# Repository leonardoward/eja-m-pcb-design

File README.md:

# EJA M v1.0

The new EJA M v1.0 is an upgrade/replacement of my older PCB designs: [Buoy A v1.0](https://github.com/leonardoward/eja-intelligent-buoy-a-electronics), [Buoy B v1.0](https://github.com/leonardoward/eja-intelligent-buoy-b-electronics), and [Onboard Gateway v1.0](https://github.com/leonardoward/eja-onboard-gateway-electronics). The design includes the following features:

- USB C Port with Electromagnetic Compatibility (EMC)
- FTDI (FT260S-U) with an Auto Reset Circuit for the ESP32
- ESP32
- GPS Module
- LoRa Transceiver
- Real-time Clock (RTC)
- Connector for a Servo Motor
- 5V 2A Stepup (for the Servo Motor)
- 3.3V Battery Charging Circuit
- Connector for a 3 axis accelerometer
- Circuit to measure the battery level
- 3.3V 3A SEPIC Converter
- On-OFF circuit for a Button
- Access to unused pins in the ESP32

This repository contains the Kicad project (including Gerber files) and a more detailed description about the implementation of the different features in the design.

## Table of Contents

1. [Hardware Design](#getting-started)
    1. [USB C Port with Electromagnetic Compatibility EMC](#usb-c-port-with-electromagnetic-compatibility-emc)
    2. [FTDI FT260S](#ftdi-ft260s)
    3. [Auto Reset Circuit for the ESP32](#auto-reset-circuit-for-the-esp32)
    4. [ESP32](#esp32)
    5. [GPS](#gps)
    6. [LoRa](#lora)
    7. [Real time Clock RTC](#real-time-clock-rtc)
    8. [Servo Motor Connector](#servo-motor-connector)
    9. [5V 2A Stepup](#5v-2a-stepup)
    10. [Accelerometer Connector](#accelerometer-connector)
    11. [Battery Charging Circuit](#battery-charging-circuit)
    12. [Battery Level](#battery-level)
    13. [3V3 3A SEPIC Converter](#3v3-3a-sepic-converter)
    14. [ON-OFF Led](#on-off-led)
    15. [ON-OFF Button Circuit](#on-off-button-circuit)
    16. [Extra Header](#extra-header)
2. [PCB Dimensions and Boundaries](#pcb-dimensions-and-boundaries)
3. [3D Model](#3d-model)
4. [Bill of Materials](#bill-of-materials)
    1. [PCB Components](#pcb-components)
    2. [Externals Components](#externals-components)

## Hardware Design

### USB C Port with Electromagnetic Compatibility EMC

Everything starts with the USB C port, we have chosen this type of USB because it's size and because of the growing trend of using this port to charge and communicate with portable devices.

We have included [Transient Voltage Suppression (TVS) diodes](https://www.digikey.com/en/products/detail/comchip-technology/CPDT6-5V4-HF/1121118) and [Ferrite Beads](https://www.digikey.com/en/products/detail/fair-rite-products-corp/2508056017Y0/8594301) to reduce the Electromagnetic Interference (EMI). These [protections for the USB port](https://www.rs-online.com/designspark/usb-port-protection) will add compliance with the [EMC regulations and standards](https://learnemc.com/emc-regulations-and-standards) from the  Federal Communications Commission (FCC) and the European Union.   

**[Back to top](#table-of-contents)**

### FTDI FT260S

The design includes the [FT260S-U](https://www.digikey.com/en/products/detail/ftdi-future-technology-devices-international-ltd/FT260S-U/6124909), a USB TO UART/I2C FTDI that will be used to program the ESP32.

**[Back to top](#table-of-contents)**

### Auto Reset Circuit for the ESP32

The design includes an auto reset circuit that uses RTS and DTR to reset and put in bootloader mode the [ESP32](https://www.digikey.com/en/products/detail/espressif-systems/ESP32-WROOM-32D-4MB/9381716). For more information about this circuit, these blogs [(1)](https://forum.micropython.org/viewtopic.php?f=18&t=4966) [(2)](https://forums.adafruit.com/viewtopic.php?f=57&p=483993#p487891) can be useful.

**[Back to top](#table-of-contents)**

### ESP32

The main microcontroller in the PCB is the [ESP32](https://www.digikey.com/en/products/detail/espressif-systems/ESP32-WROOM-32D-4MB/9381716), the following image shows the signals dedicated to the different pins. The ESP32 is connected to the [FTDI](https://www.digikey.com/en/products/detail/ftdi-future-technology-devices-international-ltd/FT260S-U/6124909), a [GPS](https://lcsc.com/product-detail/Satellite-Positioning-Modules_ZHONGKEWEI-ATGM332D-5N31_C128659.html), a [LoRa transceiver](https://www.digikey.com/en/products/detail/rf-solutions/RFM95W-915S2/6564923), a connector for a servo motor, a [real-time clock](https://www.digikey.com/en/products/detail/maxim-integrated/DS3231M-TRL/2402421?s=N4IgTCBcDaICIGUDMYkEYCyBqAKgJQBkBhHAWgDk4QBdAXyA), a circuit to measure the battery level, a connector for an [accelerometer](https://www.digikey.com/en/products/detail/adafruit-industries-llc/4097/9951931?s=N4IgTCBcDaIIwFYwA4C0KDsAWVA5AIiALoC%2BQA), and a few headers to provide access for the unused peripherals.

**[Back to top](#table-of-contents)**

### GPS

The selected GPS is the [ATGM332D-5N31](https://lcsc.com/product-detail/Satellite-Positioning-Modules_ZHONGKEWEI-ATGM332D-5N31_C128659.html), one the modules tested previously in our [Development Board for GPS Modules](https://hackaday.io/project/173457-2021-hdp-dream-team-eja/log/196269-gps-antenova-m20050-1-and-atgm332d-5n31-dev-board). The schematic is very simple, it has a decoupling capacitors (C2), a [U.FL connector](https://www.digikey.com/en/products/detail/hirose-electric-co-ltd/U-FL-R-SMT-1-10/2391570) for an external antenna (J4) and a [Coin Cell Battery Holder](https://www.digikey.com/en/products/detail/linx-technologies-inc/BAT-HLD-001-THM/3044009) (J2).

**[Back to top](#table-of-contents)**

### LoRa

The selected LoRa transceiver is the [RFM95W-915S2](https://www.digikey.com/en/products/detail/rf-solutions/RFM95W-915S2/6564923), the same module tested in our [Development Board for LoRa](https://hackaday.io/project/173457-2021-hdp-dream-team-eja/log/196116-lora-rfm95w-915s2-development-board). The schematic contains a [U.FL connector](https://www.digikey.com/en/products/detail/hirose-electric-co-ltd/U-FL-R-SMT-1-10/2391570) for an external antenna (J9).

**[Back to top](#table-of-contents)**

### Real time Clock RTC

The design includes a dedicated RTC, the [DS3231M](https://www.digikey.com/en/products/detail/maxim-integrated/DS3231M-TRL/2402421?s=N4IgTCBcDaICIGUDMYkEYCyBqAKgJQBkBhHAWgDk4QBdAXyA).

**[Back to top](#table-of-contents)**

### Servo Motor Connector

There is a 1x3 header connector for a Servo Motor, the 5V for the servo is provided by a 5V 2A Stepup.

**[Back to top](#table-of-contents)**

### 5V 2A Stepup

The design includes the [TPS61030PWR](http://digikey.com/en/products/detail/texas-instruments/TPS61030PWPR/550685?s=N4IgTCBcDa4JwDYC0BGALGlyVIHIBEQBdAXyA), a boost converter with a 4A switch current, to provide the 5V for the Servo motor. The schematic contains the components for a 5V 2A output, following the design procedure that starts on the page 13 in the datasheet.

**[Back to top](#table-of-contents)**

### Accelerometer Connector

There is a connector for the [ADXL343 3 axis accelerometer](https://www.digikey.com/en/products/detail/adafruit-industries-llc/4097/9951931?s=N4IgTCBcDaIIwFYwA4C0KDsAWVA5AIiALoC%2BQA), a 1x9 header was used even though it only manages the signals VDD, GND, SCL and SDA, in case we want to use more connections for the accelerometer in future versions.

**[Back to top](#table-of-contents)**

### Battery Charging Circuit

To charge the 3.3V battery the design includes the [TP4056](https://www.lcsc.com/product-detail/Battery-Management-ICs_TPOWER-TP4056_C382139.html), a 1A Standalone Linear Li-lon Battery Charger. The schematic includes a green led to show the user that the battery is charged and a red led to show the user that the battery is charging. There is a [Battery Holder for a 18650 battery](https://www.digikey.com/en/products/detail/mpd-memory-protection-devices/BH-18650-PC/3029216?s=N4IgTCBcDaIEIAkC0BGAHANgKwAYkAUBhJAOQBEQBdAXyA) (J5) and an additional 1x2 header (J7) in case we want to use a different 3.3V battery.  There is also a 1x2 header (J3) to use a different type of connection for the charger (instead of the USB C), for example we can connect and test a QI Wireless Charger.

**[Back to top](#table-of-contents)**

### Battery Level

The design contains a circuit to measure a battery level, it is a simple resistor divider calculated for a range of 2.7V to 4.2V, the normal range for the 18650 Li-Ion Battery that will be used in the design.

Those values for the resistor divider give the following range for the ADC:

- Maximum voltage: 4.2V * (2M / (0.806M + 2M)) = 2.99V
- Minimum voltage: 2.7V * (2M / (0.806M + 2M)) = 1.92V

That means that the ADC from the ESP32 will be reading analog values from 1.92V to 2.99V from the battery measurement circuit.

For more information about measuring lithium battery voltage visit the following [link](https://devzone.nordicsemi.com/nordic/nordic-blog/b/blog/posts/measuring-lithium-battery-voltage-with-nrf52).

**[Back to top](#table-of-contents)**

### 3V3 3A SEPIC Converter

Since the voltage of the battery can change from 2.7V (discharged) to 4.2V (charged), a SEPIC converter is included to provide a constant 3.3V to the digital circuits regardless of the changes in the input voltage from the battery. The selected SEPIC converter is the [LTC3113EFE#TRPBF](https://www.digikey.com/en/products/detail/analog-devices-inc/LTC3113EFE-TRPBF/2521714?s=N4IgTCBcDaIDIBUDCBmAjGlBRAYlgxAgEoAKAQjkggLQByAIiALoC%2BQA).

**Note**: The resistor R32 is a jumper that connects VDD to 3V3. R33 is a jumper that connects VDD to the battery. Do not solder both at the same time, it will create a short circuit between 3.3V from the SEPIC and the voltage from the battery. R32 and R33 are included just in case the SEPIC converter doesn't work and we have to connect the circuit directly to the battery.

**Summary: Do not solder R33**.

**[Back to top](#table-of-contents)**

### ON-OFF Led

There is  Green Led that turns on with the 3.3V from the SEPIC converter, it will notify the user/developer that the device is ON or OFF.

**[Back to top](#table-of-contents)**

### ON-OFF Button Circuit

The design contains a [LTC2954ITS8-1#TRPBF](https://www.digikey.com/en/products/detail/analog-devices-inc/LTC2954ITS8-1-TRPBF/1621452?s=N4IgTCBcDaIDIBUDCYCcBWALASQQZQA4BaARgGIEAlABQCEAxJBIgOQBEQBdAXyA), a pushbutton ON/OFF controller that manages the power supply (enables the 3.3V SEPIC) via a pushbutton interface.

**[Back to top](#table-of-contents)**

### Extra Header

The design includes an 1x06 header to provide access for some of the unused pins in the ESP32.

**[Back to top](#table-of-contents)**

## PCB Dimensions and Boundaries

The dimensions of the PCB are dictated by the maximum available space inside the buoy, from the enclosure design we where able to define the size of the PCB: 97.5 mm x 51.2 mm.

In the back layer there is a restricted region, that can't contain any components because the PCB is directly in contact with the enclosure in that region, those are the boundaries of the back layer. Through hole footprints where not be placed in that section, even if the footprint is placed in the front layer.

**[Back to top](#table-of-contents)**

## 3D Model

The following images show the front and back layers of the PCB.

**[Back to top](#table-of-contents)**

## Bill of Materials

### PCB Components

| Reference | Quantity |
| ------------- | ------------- |
| [PCB](https://www.pcbway.com/)  | 1 |
| [47 µF ±20% 6.3V Ceramic Capacitor 0805](https://www.digikey.com/en/products/detail/taiyo-yuden/JMK212BBJ476MG-T/4970731)  | 1 |
| [10 µF ±10% 6.3V Ceramic Capacitor 0805](https://www.digikey.com/en/products/detail/samsung-electro-mechanics/CL21A106KQCLNNC/3888062)  | 4 |
| [12 pF ±5% 50V Ceramic Capacitor 0805](https://www.digikey.com/en/products/detail/stackpole-electronics-inc/CML0805C0G120JT50V/10660016)  | 1 |
| [680 pF ±10% 25V Ceramic Capacitor 0805](https://www.digikey.com/en/products/detail/w%C3%BCrth-elektronik/885012207059/5455614)  | 1 |
| [47 pF ±5% 16V Ceramic Capacitor 0805](https://www.digikey.com/en/products/detail/w%C3%BCrth-elektronik/885012007014/5453673)  | 3 |
| [100 µF ±20% 6.3V Ceramic Capacitor 1210](https://www.digikey.com/en/products/detail/murata-electronics/GRM32EE70J107ME15L/5027618)  | 1 |
| [0.1 µF ±10% 50V Ceramic Capacitor 0805](https://www.digikey.com/en/products/detail/avx-corporation/08055C104KAT2A/563505)  | 3 |
| [4.7 µF ±10% 6.3V Ceramic Capacitor 0805](https://www.digikey.com/en/products/detail/samsung-electro-mechanics/CL21A475KQFNNNE/3886856)  | 1 |
| [1 µF ±10% 16V Ceramic Capacitor 0805](https://www.digikey.com/en/products/detail/yageo/CC0805KKX7R7BB105/2103103)  | 4 |
| [2.2 µF ±10% 10V Ceramic Capacitor 0805](https://www.digikey.com/en/products/detail/samsung-electro-mechanics/CL21B225KPFNNNE/3886846)  | 1 |
| [220 µF Tantalum Capacitors 10V 2917](https://www.digikey.com/en/products/detail/nemco/PCT220-10HK/13236441)  | 1 |
| [0.033 µF ±10% 50V Ceramic Capacitor 0805](https://www.digikey.com/en/products/detail/w%C3%BCrth-elektronik/885012207095/5453932)  | 1 |
| [Orange 601nm LED - Discrete 2.1V 0805](https://www.digikey.com/en/products/detail/sunled/XZMOK54W-1/4745796)  | 1 |
| [Green 520nm LED - Discrete 3.2V 0805](https://www.digikey.com/en/products/detail/w%C3%BCrth-elektronik/150080GS75000/4489915)  | 2 |
| [TVS Diode 15V Clamp 5A (8/20µs) SOT-23-6](https://www.digikey.com/en/products/detail/comchip-technology/CPDT6-5V4-HF/1121118)  | 1 |
| [Red 630nm LED - Discrete 1.9V 0805](https://www.digikey.com/en/products/detail/w%C3%BCrth-elektronik/150080SS75000/4489921)  | 1 |
| [Yellow 590nm LED - Discrete 2V 0805](https://www.digikey.com/en/products/detail/everlight-electronics-co-ltd/QTLP630C3TR/2675901)  | 1 |
| [1 Signal Line Ferrite Bead 0805 300mA 350mOhm](https://www.digikey.com/en/products/detail/fair-rite-products-corp/2508056017Y0/8594301)  | 2 |
| [USB-C USB 3.2 Gen 2 Receptacle Connector](https://www.digikey.com/en/products/detail/cui-devices/UJ31-CH-G2-SMT-TR/8024057)  | 1 |
| [Battery Retainer Coin, 20.0mm 1 Cell PC Pin](https://www.digikey.com/en/products/detail/linx-technologies-inc/BAT-HLD-001-THM/3044009)  | 1 |
| [U.FL (UMCC) Connector Receptacle](https://www.digikey.com/en/products/detail/hirose-electric-co-ltd/U-FL-R-SMT-1-10/2391570)  | 2 |
| [Battery Holder (Open) 18650 1 Cell PC Pin](https://www.digikey.com/en/products/detail/mpd-memory-protection-devices/BH-18650-PC/3029216)  | 1 |
| [2 Position Terminal Block Horizontal](https://www.digikey.com/en/products/detail/on-shore-technology-inc/OSTTC022162/614558)  | 1 |
| [2.2 µH Inductor 15 A 7mOhm Max](https://www.digikey.com/en/products/detail/sumida-america-components-inc/104CDMCCDS-2R2MC/5812436)  | 1 |
| [5.5 µH Inductor 10 A 10.3mOhm](https://www.digikey.com/en/products/detail/w%C3%BCrth-elektronik/744325550/1638576)  | 1 |
| [Bipolar (BJT) Transistor NPN 30V 600mA SOT-23-3](https://www.digikey.com/en/products/detail/onsemi/MMBT2222LT1G/919595)  | 3 |
| [1 MOhms ±1% 0.125W Chip Resistor 0805](https://www.digikey.com/en/products/detail/stackpole-electronics-inc/RMCF0805FT1M00/1760080)  | 2 |
| [90.9 kOhms ±1% 0.125W Chip Resistor 0805](https://www.digikey.com/en/products/detail/stackpole-electronics-inc/RMCF0805FT90K9/1760265)  | 1 |
| [620 Ohms ±5% 0.125W Chip Resistor 0805](https://www.digikey.com/en/products/detail/yageo/RC0805JR-07620RL/728357)  | 5 |
| [5.1 KOhms ±1% 0.125W Chip Resistor 0805](https://www.digikey.com/en/products/detail/stackpole-electronics-inc/RMCF0805FT5K10/1760394)  | 3 |
| [49.9 KOhms ±1% 0.125W Chip Resistor 0805](https://www.digikey.com/en/products/detail/stackpole-electronics-inc/RMCF0805FT49K9/1760272)  | 1 |
| [825 kOhms ±0.5% 0.125W Chip Resistor 0805](https://www.digikey.com/en/products/detail/panasonic-electronic-components/ERA-6AED8253V/3481309)  | 1 |
| [182 kOhms ±1% 0.25W Chip Resistor 0805](https://www.digikey.com/en/products/detail/koa-speer-electronics-inc/RK73H2ATTD1823F/10234151)  | 1 |
| [1.2 kOhms ±5% 0.125W Chip Resistor 0805](https://www.digikey.com/en/products/detail/yageo/RC0805JR-071K2L/728224)  | 1 |
| [6.49 kOhms ±1% 0.125W Chip Resistor 0805](https://www.digikey.com/en/products/detail/panasonic-electronic-components/ERJ-6ENF6491V/111437)  | 1 |
| [27 Ohms ±1% 0.125W Chip Resistor 0805](https://www.digikey.com/en/products/detail/stackpole-electronics-inc/RMCF0805FT27R0/1712920)  | 2 |
| [10 kOhms ±1% 0.125W Chip Resistor 0805](https://www.digikey.com/en/products/detail/vishay-dale/CRCW080510K0FKEAC/7928398)  | 10 |
| [1 kOhms ±1% 0.125W Chip Resistor 0805](https://www.digikey.com/en/products/detail/stackpole-electronics-inc/RMCF0805FT1K00/1760090)  | 1 |
| [1.8 MOhms ±1% 0.125W Chip Resistor 0805](https://www.digikey.com/en/products/detail/panasonic-electronic-components/ERJ-6ENF1804V/282715)  | 1 |
| [390 kOhms ±1% 0.125W Chip Resistor 0805](https://www.digikey.com/en/products/detail/yageo/RC0805FR-07390KL/727903)  | 1 |
| [806 kOhms ±1% 0.125W Chip Resistor 0805](https://www.digikey.com/en/products/detail/panasonic-electronic-components/ERJ-6ENF8063V/112197)  | 1 |
| [2 MOhms ±1% 0.125W Chip Resistor 0805](https://www.digikey.com/en/products/detail/vishay-dale/CRCW08052M00FKECC/7928551)  | 1 |
| [180 kOhms ±0.5% 0.1W Chip Resistor 0805](https://www.digikey.com/en/products/detail/susumu/RR1220P-184-D/432345)  | 1 |
| [0 Ohms Jumper 0.125W Chip Resistor 0805](https://www.digikey.com/en/products/detail/yageo/RC0805JR-070RL/728216)  | 2 |
| [ATGM332D-5N31 GNSS Series GPS+BDS 12.2x16x2.4mm](https://www.lcsc.com/product-detail/Satellite-Positioning-Modules_ZHONGKEWEI-ATGM332D-5N31_C128659.html)  | 1 |
| [Buck-Boost Switching Regulator 1.8V 1 Output 3A](https://www.digikey.com/en/products/detail/analog-devices-inc/LTC3113EFE-TRPBF/2521714)  | 1 |
| [TP4056 ESOP-8 Battery Management](https://www.lcsc.com/product-detail/Battery-Management-ICs_TPOWER-TP4056_C382139.html)  | 1 |
| [ESP32-WROOM-32D (4MB)](https://www.digikey.com/en/products/detail/espressif-systems/ESP32-WROOM-32D-4MB/9381716)  | 1 |
| [FTDI USB Bridge, USB to I²C/UART USB 2.0 I²C, UART Interface 28-TSSOP](https://www.digikey.com/en/products/detail/ftdi-future-technology-devices-international-ltd/FT260S-U/6124909)  | 1 |
| [TPS61030PWPR Boost Switching Regulator IC Positive Adjustable 1.8V 1 Output 3.6A (Switch)](https://www.digikey.com/en/products/detail/texas-instruments/TPS61030PWPR/550685)  | 1 |
| [RFM95W-915S2-ND LoRa Transceiver Module 915MHz](https://www.digikey.com/en/products/detail/rf-solutions/RFM95W-915S2/6564923)  | 1 |
| [DS3231M+TRL Real Time Clock I²C, 2-Wire Serial](https://www.digikey.com/en/products/detail/maxim-integrated/DS3231M-TRL/2402421)  | 1 |
| [Power Supply On/Off Controller Push Button](https://www.digikey.com/en/products/detail/analog-devices-inc/LTC2954ITS8-1-TRPBF/1621452)  | 1 |
| [Connector Header Through Hole 40 position (2.54mm)](https://www.digikey.com/en/products/detail/sullins-connector-solutions/PREC040SFAN-RC/2774934)  | 1 |

### Externals Components

| Reference | Quantity |
| ------------- | ------------- |
| [SERVOMOTOR RC 5V HIGH TORQUE](https://www.digikey.com/products/es?keywords=1528-1084-ND)  | 1 |
| [CR2032 Lithium Coin Cell Battery](https://www.adafruit.com/product/654)  | 1 |
| [18650 Lithium-Ion 3.7V Battery Rechargeable 3.4Ah](https://www.digikey.com/en/products/detail/ultralast/LION-1865-34/13692714)  | 1 |
| [ADXL343 - Triple-Axis Accelerometer](https://www.digikey.com/en/products/detail/adafruit-industries-llc/4097/9951931)  | 1 |

For more information about the BOM including prices and different comparisons with my previous designs visit the following [link](https://hackaday.io/project/173457-2021-hdp-dream-team-eja/log/198071-eja-m-v10-bill-of-materials).

**[Back to top](#table-of-contents)**

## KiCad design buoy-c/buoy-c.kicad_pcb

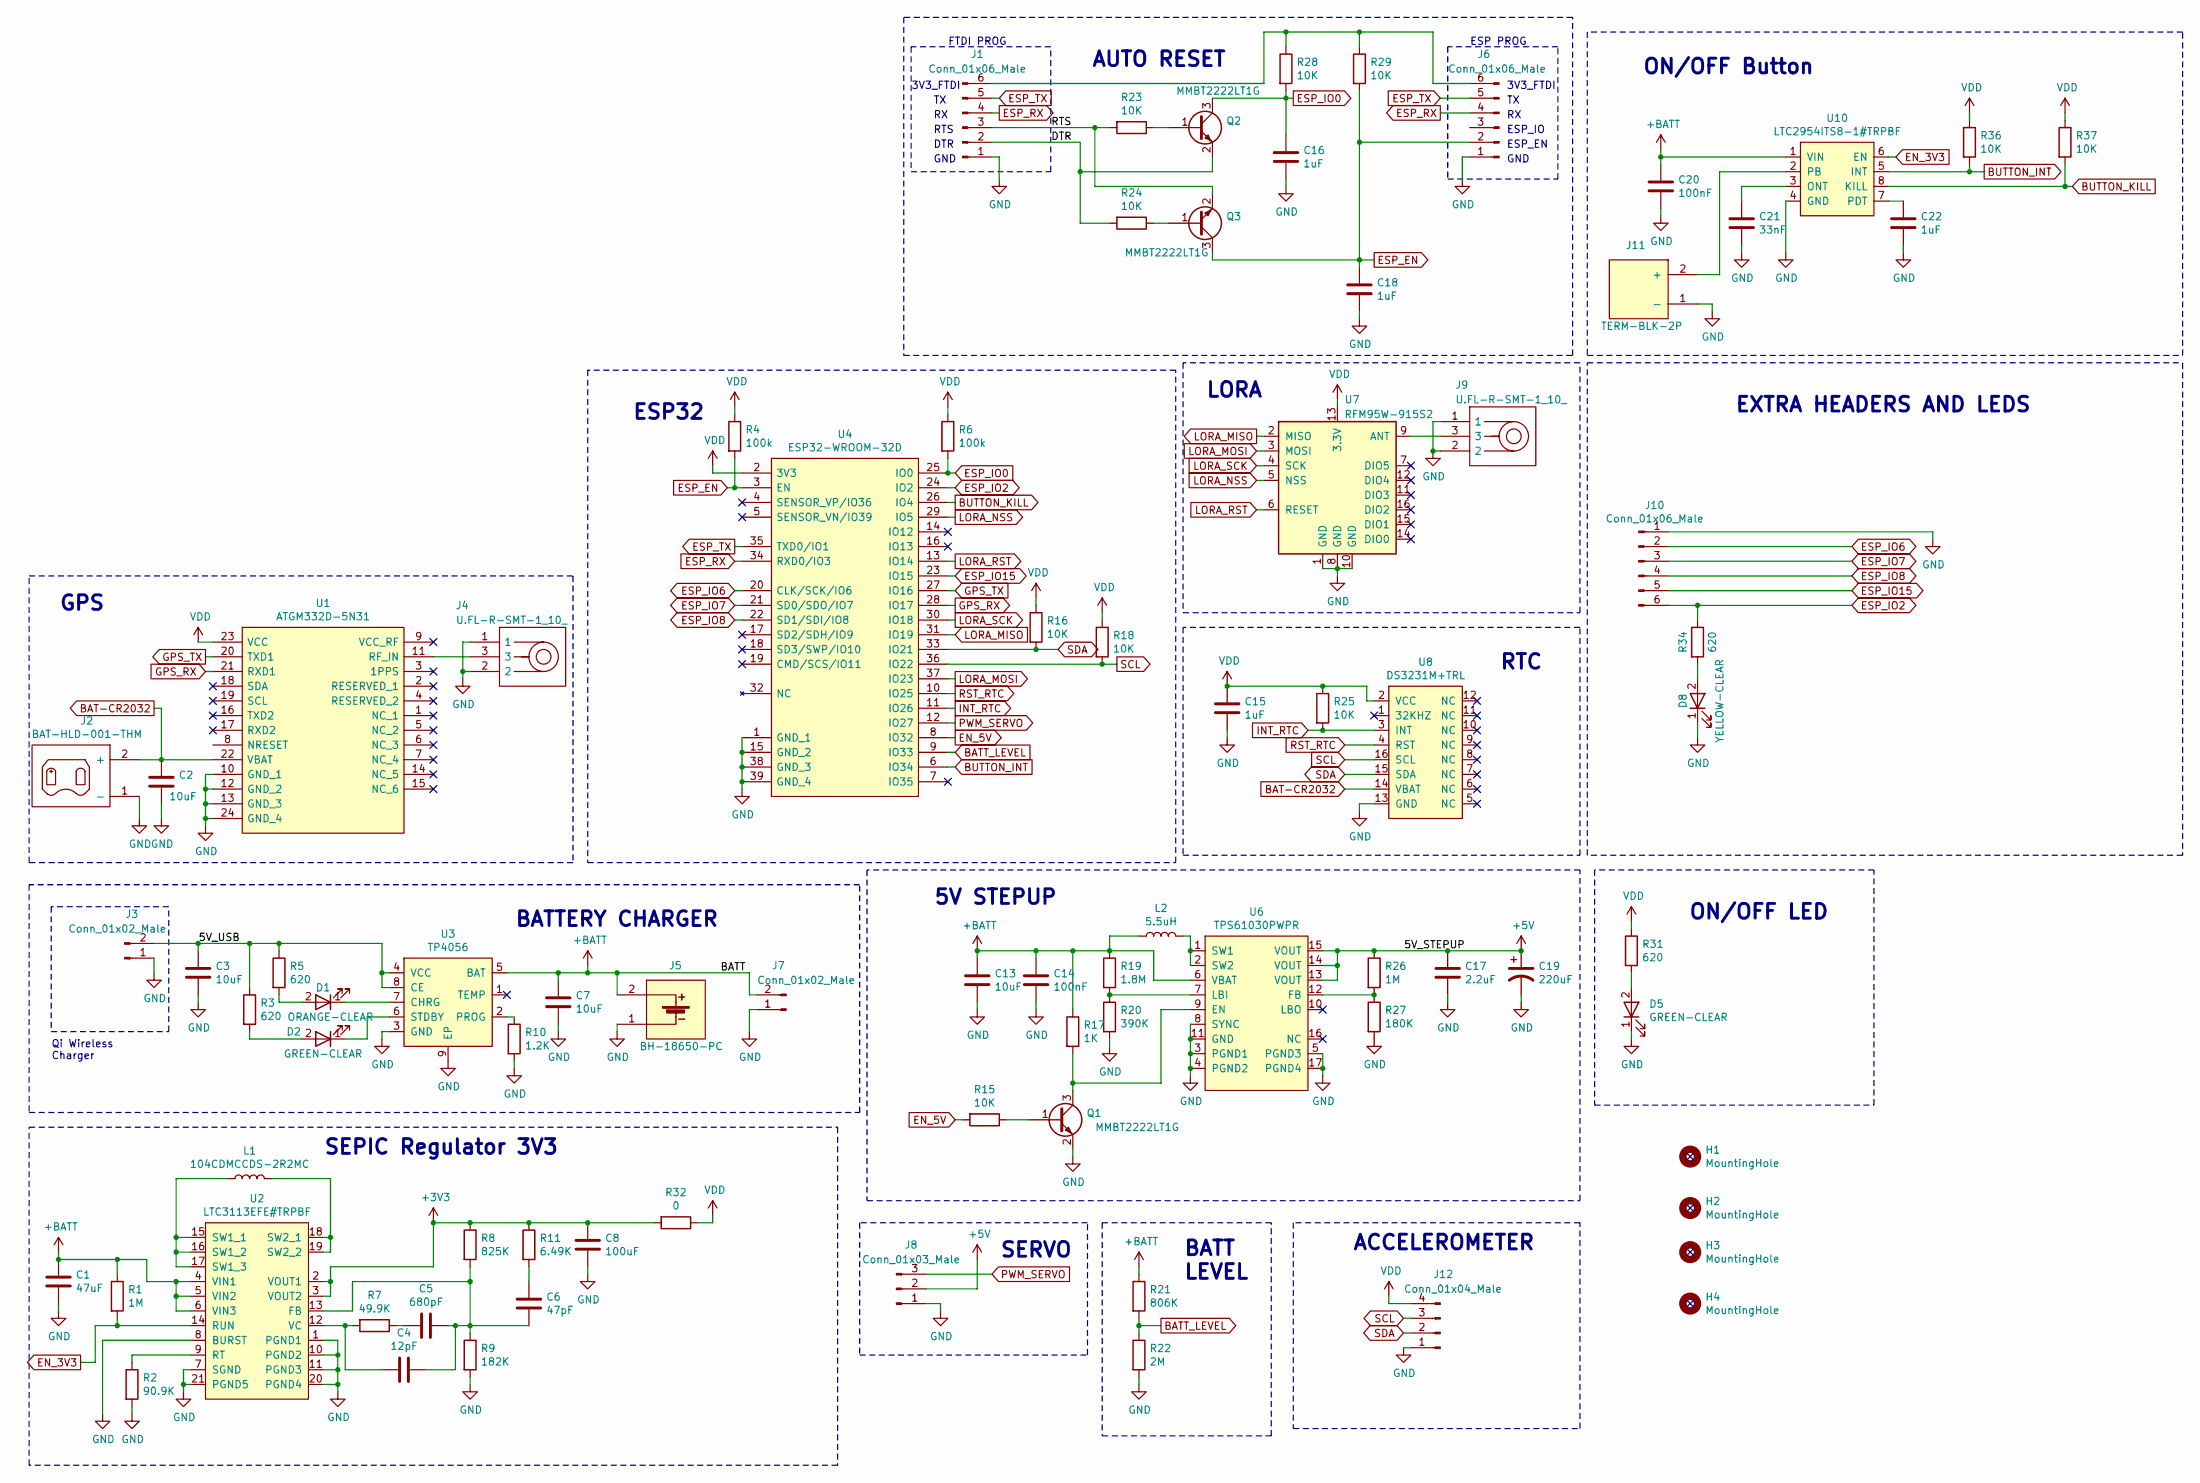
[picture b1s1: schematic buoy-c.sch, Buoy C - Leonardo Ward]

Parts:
C1: 47uF; C_0805_2012Metric; Manufacturer Part Number JMK212BBJ476MG-T
C2, C3, C7, C13: 10uF; C_0805_2012Metric; Manufacturer Part Number CL21A106KQCLNNC
C4: 12pF; C_0805_2012Metric; Manufacturer Part Number CML0805C0G120JT50V
C5: 680pF; C_0805_2012Metric; Manufacturer Part Number 885012207059
C6: 47pF; C_0805_2012Metric; Manufacturer_Part_Number 885012007014
C8: 100uF; C_1210_3225Metric; Manufacturer Part Number GRM32EE70J107ME15L
C14, C20: 100nF; C_0805_2012Metric; Manufacturer_Part_Number 08055C104KAT2A
C15, C16, C18, C22: 1uF; C_0805_2012Metric; Manufacturer_Part_Number CL21B105KPFNNNE
C17: 2.2uF; C_0805_2012Metric; Manufacturer Part Number CL21B225KPFNNNE
C19: 220uF; C-2917-7343-Metric; Manufacturer Part Number PCT220/10HK
C21: 33nF; C_0805_2012Metric; Manufacturer Part Number 885012207095
D1: ORANGE-CLEAR; LED_0805_2012Metric; Manufacturer Part Number XZMOK54W-1
D2, D5: GREEN-CLEAR; LED_0805_2012Metric; Manufacturer Part Number 150080VS75000
D8: YELLOW-CLEAR; LED_0805_2012Metric; Manufacturer Part Number QTLP630C3TR
H1, H2, H3, H4: MountingHole; MountingHole_3.5mm
J1, J6, J10: Conn_01x06_Male; PinHeader_1x06_P2.54mm_Vertical
J2: BAT-HLD-001-THM; BATHLD001THM; Manufacturer_Part_Number BAT-HLD-001-THM
J3, J7: Conn_01x02_Male; PinHeader_1x02_P2.54mm_Vertical
J4, J9: U.FL-R-SMT-1_10_; Manufacturer Part Number U.FL-R-SMT-1(10)
J5: BH-18650-PC; BatteryHolder_MPD_BH-18650-PC2; Manufacturer_Part_Number BH-18650-PC
J8: Conn_01x03_Male; PinHeader_1x03_P2.54mm_Vertical
J11: TERM-BLK-2P; TerminalBlock_bornier-2_P5.08mm
J12: Conn_01x04_Male; PinHeader_1x04_P2.54mm_Vertical
L1: 104CDMCCDS-2R2MC; L-11.5x10.3x4; Manufacturer_Part_Number 104CDMCCDS-2R2MC
L2: 5.5uH; L-10.5x10.2x5; Manufacturer Part Number 744325550
Q1, Q2, Q3: MMBT2222LT1G; SOT-23; Manufacturer_Part_Number MMBT2222LT1G
R1, R26: 1M; R_0805_2012Metric; Manufacturer Part Number RMCF0805FT1M00
R2: 90.9K; R_0805_2012Metric; Manufacturer Part Number RMCF0805FT90K9
R3, R5, R31, R34: 620; R_0805_2012Metric; Manufacturer_Part_Number RC0805JR-07620RL
R4, R6: 100k; R_0805_2012Metric_Pad1.20x1.40mm_HandSolder; Manufacturer_Part_Number RMCF0805FG100K
R7: 49.9K; R_0805_2012Metric; Manufacturer Part Number RMCF0805FT49K9
R8: 825K; R_0805_2012Metric; Manufacturer Part Number ERA-6AED8253V
R9: 182K; R_0805_2012Metric; Manufacturer Part Number RK73H2ATTD1823F
R10: 1.2K; R_0805_2012Metric_Pad1.20x1.40mm_HandSolder; Manufacturer Part Number RC0805JR-071K2L
R11: 6.49K; R_0805_2012Metric; Manufacturer Part Number ERJ-6ENF6491V
R15, R16, R18, R23, R24, R25, R28, R29, R36, R37: 10K; R_0805_2012Metric; Manufacturer_Part_Number CRCW080510K0FKEAC
R17: 1K; R_0805_2012Metric; Manufacturer_Part_Number RMCF0805FT1K00
R19: 1.8M; R_0805_2012Metric; Manufacturer Part Number ERJ-6ENF1804V
R20: 390K; R_0805_2012Metric; Manufacturer Part Number RC0805FR-07390KL
R21: 806K; C_0805_2012Metric; Manufacturer Part Number ERJ-6ENF8063V
R22: 2M; C_0805_2012Metric; Manufacturer Part Number CRCW08052M00FKECC
R27: 180K; R_0805_2012Metric; Manufacturer Part Number RR1220P-184-D
R32: 0; R_0805_2012Metric; Manufacturer Part Number RC0805JR-070RL
U1: ATGM332D-5N31; ATGM332D5N31; Manufacturer_Part_Number ATGM332D-5N31; LCSC C128659
U2: LTC3113EFE#TRPBF; HTSSOP-20-1EP_4.4x6.5mm_P0.65mm_EP3.4x6.5mm_Mask2.75x3.43mm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; Manufacturer Part Number LTC3113EFE#TRPBF
U3: TP4056; ESOP-8; LCSC C382139
U4: ESP32-WROOM-32D; Manufacturer_Part_Number ESP32-WROOM-32D; LCSC C473012
U6: TPS61030PWPR; HTSSOP-16-1EP_4.4x5mm_P0.65mm_EP3.4x5mm_Mask3x3mm_ThermalVi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; Manufacturer Part Number TPS61030PWPR
U7: RFM95W-915S2; HOPERF_RFM9XW_SMD
U8: DS3231M+TRL; SOIC-16W_7.5x10.3mm_P1.27mm; Manufacturer Part Number DS3231M+TRL
U10: LTC2954ITS8-1#TRPBF; TSOT-23-8_HandSoldering; Manufacturer Part Number LTC2954ITS8-1#TRPBF

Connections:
+3V3: C8.1, R8.1, R11.1, R32.2, U2.2 (VOUT1), U2.3 (VOUT2)
+5V: C17.1, C19.1, J8.2, R26.1, U6.13 (VOUT), U6.14 (VOUT), U6.15 (VOUT)
+BATT: C1.1, C7.1, C13.1, C14.1, C20.1, J5.2 (+), J7.2, L2.1, R1.1, R17.1, R19.1, R21.1, U2.4 (VIN1), U2.5 (VIN2), U2.6 (VIN3), U3.5 (BAT), U6.6 (VBAT), U10.1 (VIN)
/5V_USB: C3.1, J3.2, R3.1, R5.1, U3.4 (VCC), U3.8 (CE)
/DTR: J1.2, Q2.2 (E), R24.2
/RTS: J1.3, Q3.2 (E), R23.2
BAT-CR2032: C2.1, J2.2 (+), U1.22 (VBAT), U8.14 (VBAT)
BATT_LEVEL: R21.2, R22.1, U4.9 (IO33)
BUTTON_INT: R36.2, U4.6 (IO34), U10.5 (INT)
BUTTON_KILL: R37.2, U4.26 (IO4), U10.8 (KILL)
EN_3V3: R1.2, U2.14 (RUN), U10.6 (EN)
EN_5V: R15.2, U4.8 (IO32)
ESP_EN: C18.1, J6.2, Q3.3 (C), R4.2, R29.2, U4.3 (EN)
ESP_IO0: C16.1, Q2.3 (C), R6.2, R28.2, U4.25 (IO0)
ESP_IO2: J10.6, R34.1, U4.24 (IO2)
ESP_IO6: J10.2, U4.20 (CLK/SCK/IO6)
ESP_IO7: J10.3, U4.21 (SD0/SDO/IO7)
ESP_IO8: J10.4, U4.22 (SD1/SDI/IO8)
ESP_IO15: J10.5, U4.23 (IO15)
ESP_RX: J1.4, J6.4, U4.34 (RXD0/IO3)
ESP_TX: J1.5, J6.5, U4.35 (TXD0/IO1)
GND: C1.2, C2.2, C3.2, C7.2, C8.2, C13.2, C14.2, C15.2, C16.2, C17.2, C18.2, C19.2, C20.2, C21.2, C22.2, D5.1 (K), D8.1 (K), J1.1, J2.1 (-), J3.1, J4.1, J4.2, J5.1 (-), J6.1, J7.1, J8.1, J9.1, J9.2, J10.1, J11.1 (-), J12.1, Q1.2 (E), R2.2, R9.2, R10.2, R20.2, R22.2, R27.2, U1.10 (GND_1), U1.12 (GND_2), U1.13 (GND_3), U1.24 (GND_4), U2.1 (PGND1), U2.7 (SGND), U2.8 (BURST), U2.10 (PGND2), U2.11 (PGND3), U2.20 (PGND4), U2.21 (PGND5), U3.3 (GND), U3.9 (EP), U4.1 (GND_1), U4.15 (GND_2), U4.38 (GND_3), U4.39 (GND_4), U6.3 (PGND1), U6.4 (PGND2), U6.5 (PGND3), U6.8 (SYNC), U6.11 (GND), U6.17 (PGND4), U7.1 (GND), U7.8 (GND), U7.10 (GND), U8.13 (GND), U10.4 (GND)
GPS_RX: U1.21 (RXD1), U4.28 (IO17)
GPS_TX: U1.20 (TXD1), U4.27 (IO16)
INT_RTC: R25.2, U4.11 (IO26), U8.3 (INT)
LORA_MISO: U4.31 (IO19), U7.2 (MISO)
LORA_MOSI: U4.37 (IO23), U7.3 (MOSI)
LORA_NSS: U4.29 (IO5), U7.5 (NSS)
LORA_RST: U4.13 (IO14), U7.6 (RESET)
LORA_SCK: U4.30 (IO18), U7.4 (SCK)
unnamed: C4.1, C5.1, C6.2, R8.2, R9.1, U2.13 (FB)
unnamed: C4.2, R7.2, U2.12 (VC)
unnamed: C5.2, R7.1
unnamed: C6.1, R11.2
unnamed: C21.1, U10.3 (ONT)
unnamed: C22.1, U10.7 (PDT)
unnamed: D1.1 (K), U3.7 (CHRG)
unnamed: D1.2 (A), R5.2
unnamed: D2.1 (K), U3.6 (STDBY)
unnamed: D2.2 (A), R3.2
unnamed: D5.2 (A), R31.2
unnamed: D8.2 (A), R34.2
unnamed: J1.6, J6.6, R28.1, R29.1
unnamed: J4.3, U1.11 (RF_IN)
unnamed: J9.3, U7.9 (ANT)
unnamed: J11.2 (+), U10.2 (PB)
unnamed: L1.1, U2.15 (SW1_1), U2.16 (SW1_2), U2.17 (SW1_3)
unnamed: L1.2, U2.18 (SW2_1), U2.19 (SW2_2)
unnamed: L2.2, U6.1 (SW1), U6.2 (SW2)
unnamed: Q1.1 (B), R15.1
unnamed: Q1.3 (C), R17.2, U6.9 (EN)
unnamed: Q2.1 (B), R23.1
unnamed: Q3.1 (B), R24.1
unnamed: R2.1, U2.9 (RT)
unnamed: R10.1, U3.2 (PROG)
unnamed: R19.2, R20.1, U6.7 (LBI)
unnamed: R26.2, R27.1, U6.12 (FB)
PWM_SERVO: J8.3, U4.12 (IO27)
RST_RTC: U4.10 (IO25), U8.4 (RST)
SCL: J12.3, R18.2, U4.36 (IO22), U8.16 (SCL)
SDA: J12.2, R16.2, U4.33 (IO21), U8.15 (SDA)
VDD: C15.1, J12.4, R4.1, R6.1, R16.1, R18.1, R25.1, R31.1, R32.1, R36.1, R37.1, U1.23 (VCC), U4.2 (3V3), U7.13 (3.3V), U8.2 (VCC)

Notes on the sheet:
AUTO RESET
LORA
GPS
RTC
ESP32
BATTERY CHARGER
Qi Wireless Charger
SEPIC Regulator 3V3
5V STEPUP
SERVO
BATT LEVEL
ACCELEROMETER
ON/OFF Button
ON/OFF LED
EXTRA HEADERS AND LEDS
GND
DTR
RTS
3V3_FTDI
FTDI PROG
ESP_IO
ESP_EN
ESP PROG

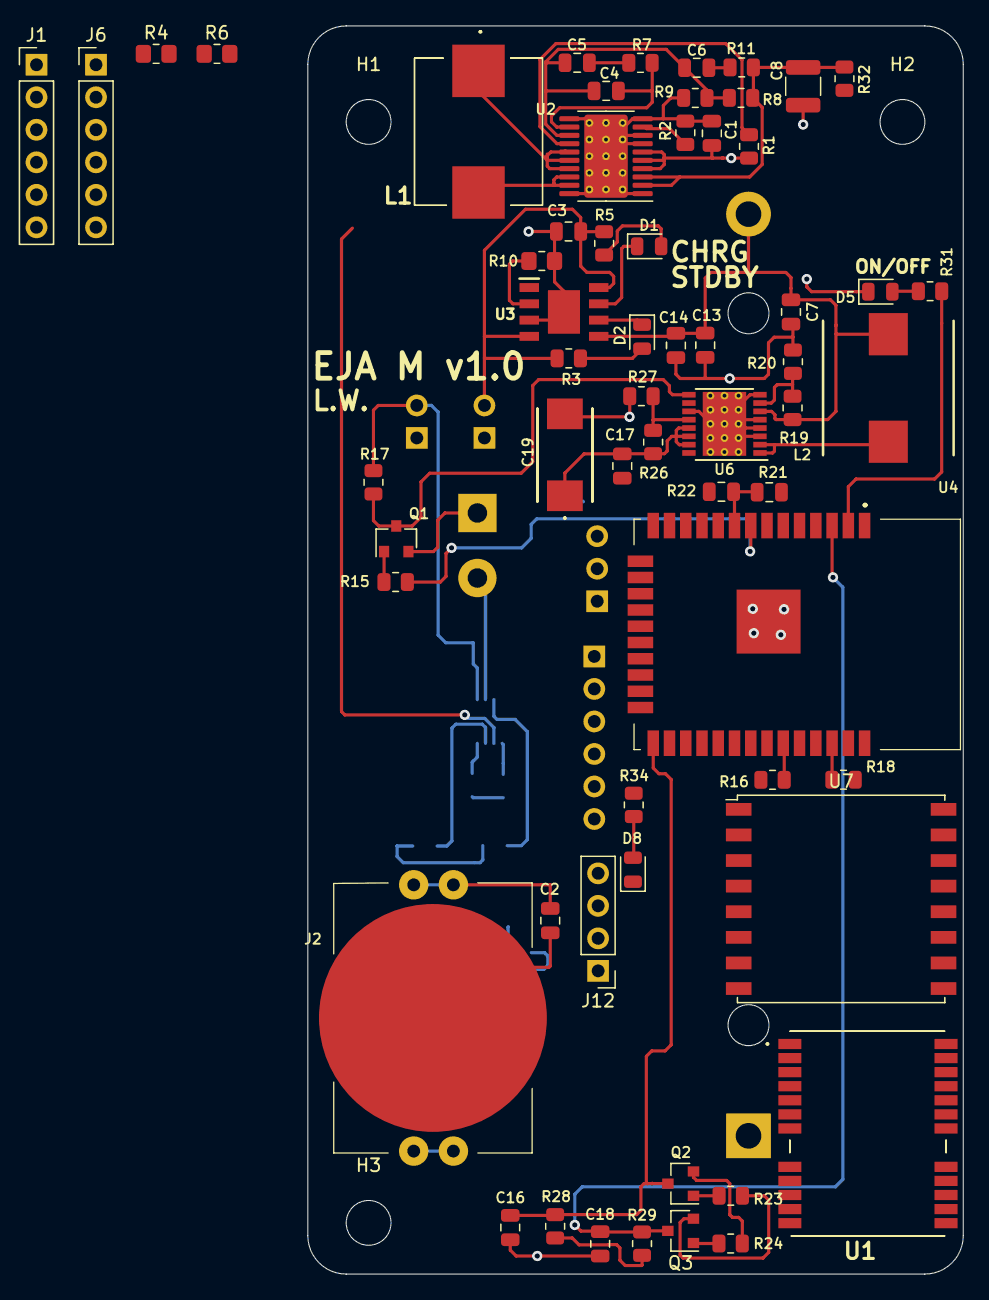
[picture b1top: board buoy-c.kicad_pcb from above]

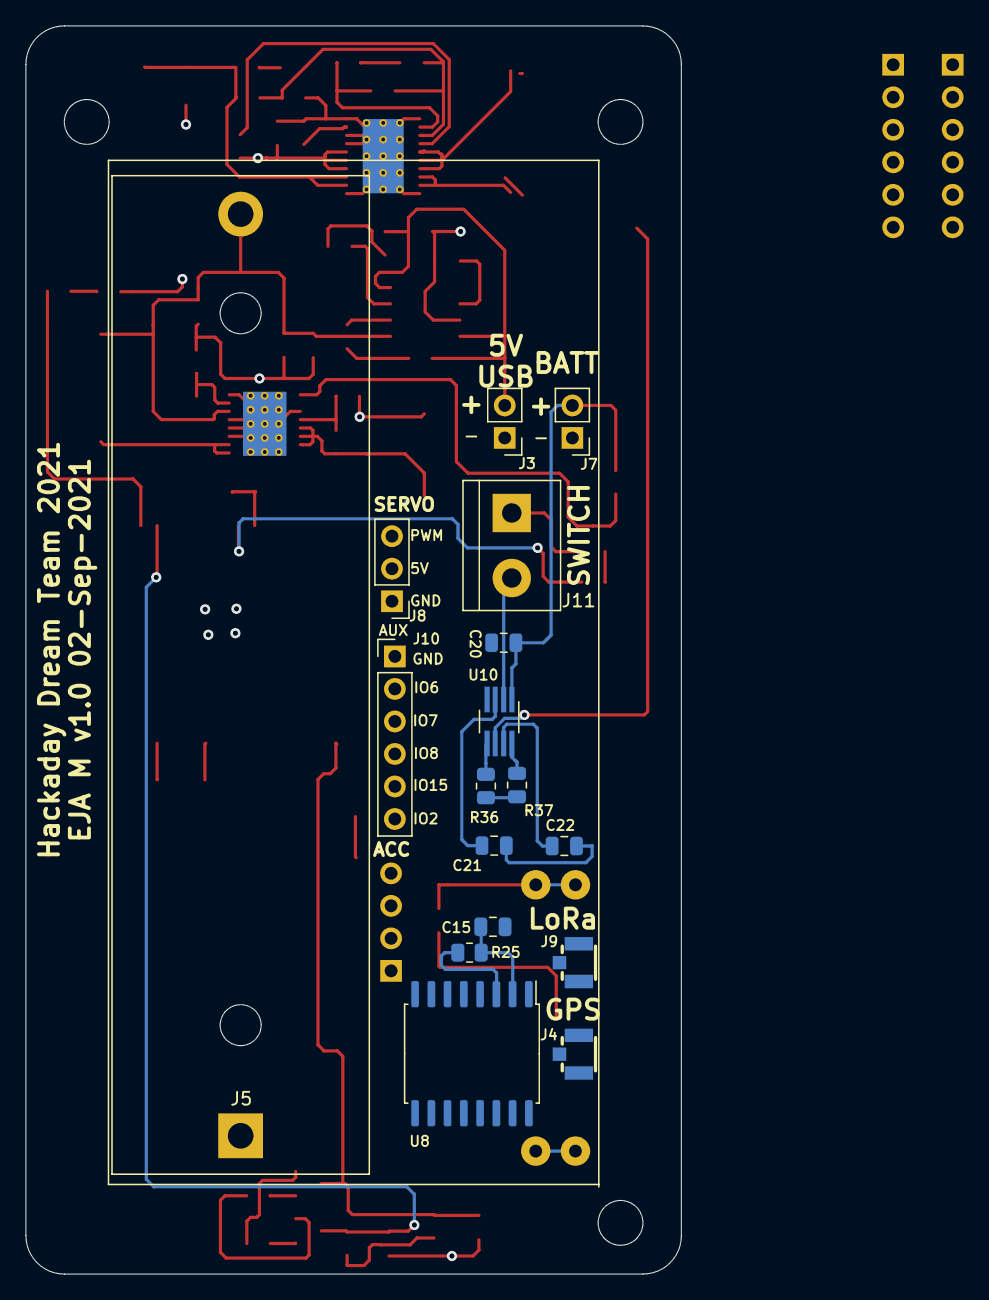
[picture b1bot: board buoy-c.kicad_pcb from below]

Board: 4 copper layers, 51.2 x 97.5 mm, 81 parts (17 on the bottom side), 62 nets.

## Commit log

2021-08-22 Added USB C, FTDI, auto reset, LoRa, GPS and ESP32 to the schematic
2021-08-27 Added regulator, stepup, accelerometer, battery charger, servo and battery measurement
2021-08-27 Added schematic
2021-08-30 Defined board shape, placed components in the PCB
2021-08-31 Placed components in the PCB
2021-09-02 Finished routing, solved unconnected
2021-09-02 Solved important errors
2021-09-02 Added missing 3d Models
2021-09-03 Added gerber files
2021-10-13 Added images
2021-10-14 Added readme
2021-10-14 Fixed links in readme
2021-10-14 Added BOM
2021-10-14 Added BOM to the menu
2021-11-06 Changed readme
2022-02-11 Removed FTDI and added extra headers
2022-02-20 Re routed Sepic converter
2022-02-20 Changed routing of the sepic converter
2022-09-02 Changed toutes of the PCB, including routes width
